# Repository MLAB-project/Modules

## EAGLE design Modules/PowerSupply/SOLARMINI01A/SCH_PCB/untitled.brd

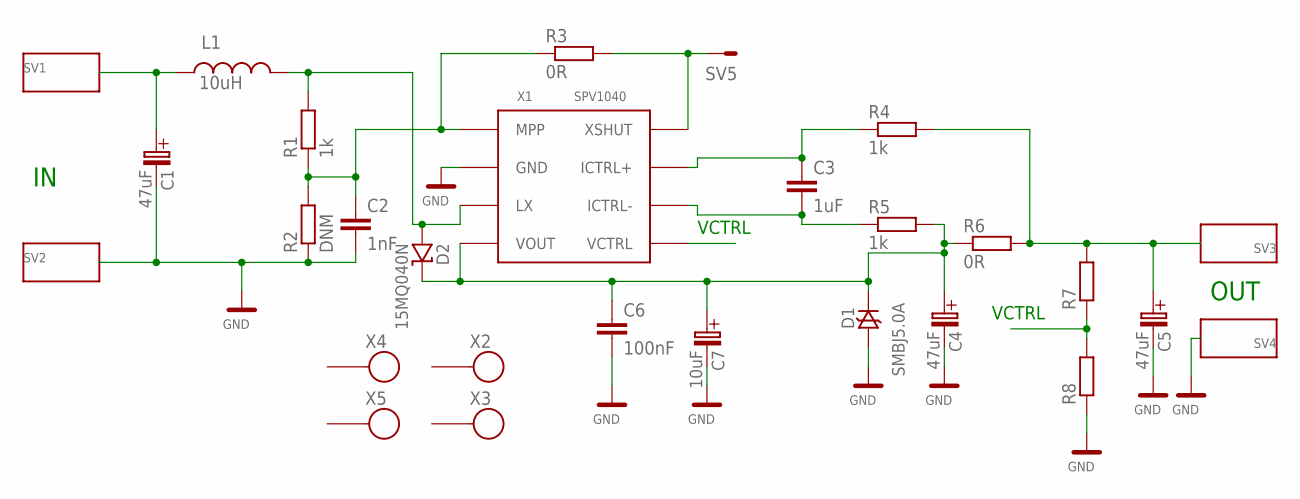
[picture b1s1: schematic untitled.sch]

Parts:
C1, C4, C5: 47uF; C
C2: 1nF; C0805
C3: 1uF; C0805
C6: 100nF; C0805
C7: 10uF; B
D1: SMBJ5.0A; SMB
D2: 15MQ040N; SMA
L1: 10uH; DE1205-10
R1, R4, R5: 1k; 0805
R2: DNM; 0805
R3, R6: 0R; 1206
R7, R8: R0805; 0805
SV1, SV2, SV3, SV4: WAGO256
SV5: MA01-1
X1: SPV1040; TSSOP8
X2, X3, X4, X5: SROUB3M

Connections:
GND: C1.- (C_EL-), C2.2, C4.- (C_EL-), C5.- (C_EL-), C6.2, C7.- (C_EL-), D1.A, R2.1, R8.1, SV2.1, SV2.A1, SV4.1, SV4.A1, X1.2 (GND)
unnamed: C1.+ (C_EL+), L1.P$1 (1), SV1.1, SV1.A1
unnamed: R3.2, SV5.1, X1.8 (XSHUT)
unnamed: C2.1, R1.1, R2.2, R3.1, X1.1 (MPP)
unnamed: C3.1, R4.1, X1.7 (ICTRL+)
unnamed: C4.+ (C_EL+), C6.1, C7.+ (C_EL+), D1.K, D2.K, R5.2, R6.1, X1.4 (VOUT)
unnamed: D2.A, L1.P$2 (2), R1.2, X1.3 (LX)
unnamed: C5.+ (C_EL+), R4.2, R6.2, R7.2, SV3.1, SV3.A1
unnamed: C3.2, R5.1, X1.6 (ICTRL-)
VCTRL: R7.1, R8.2, X1.5 (VCTRL)

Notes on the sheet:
VCTRL
OUT

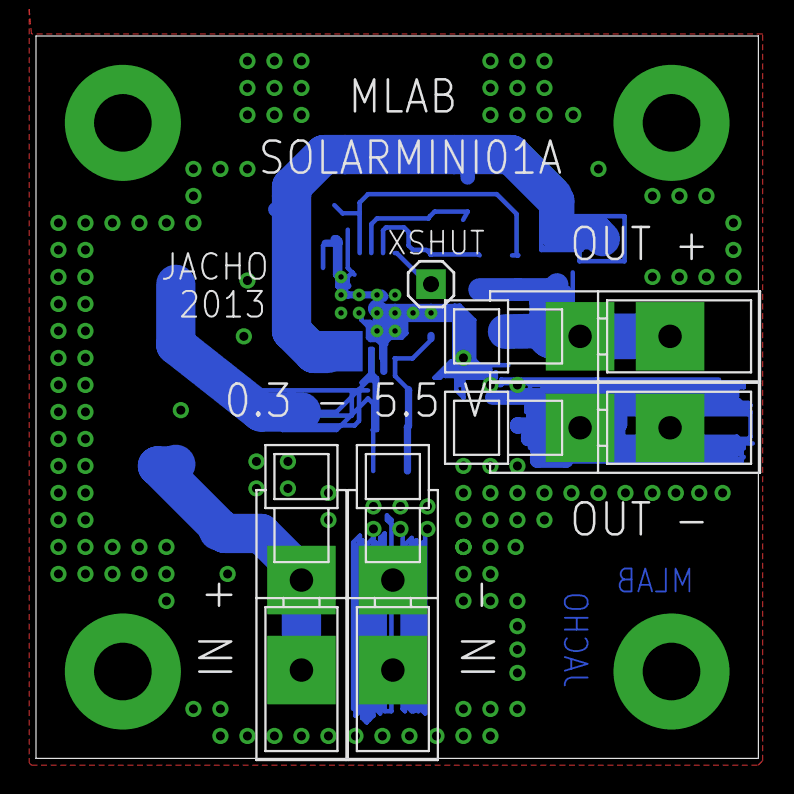
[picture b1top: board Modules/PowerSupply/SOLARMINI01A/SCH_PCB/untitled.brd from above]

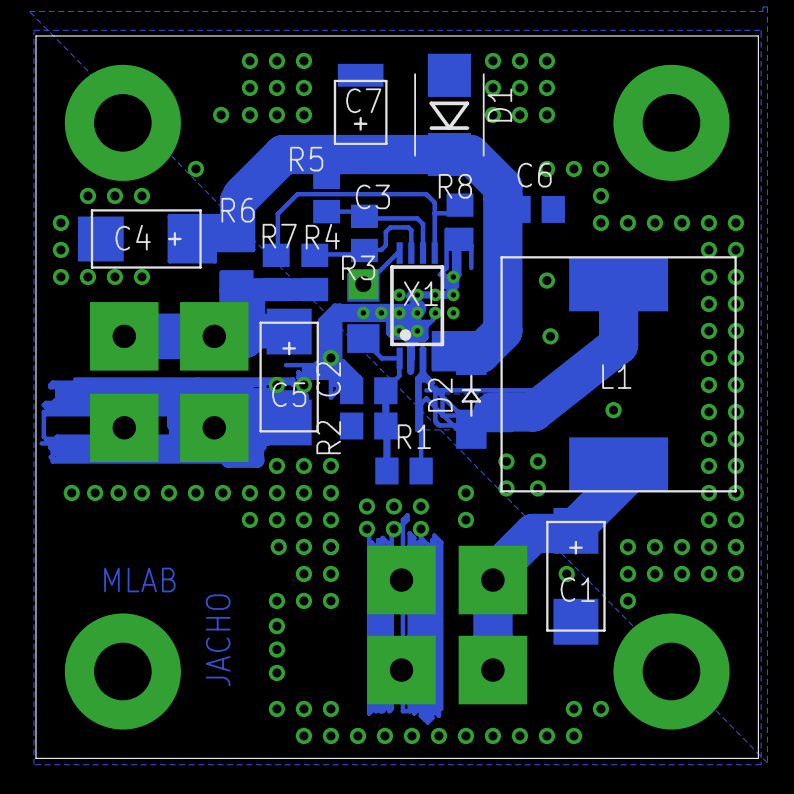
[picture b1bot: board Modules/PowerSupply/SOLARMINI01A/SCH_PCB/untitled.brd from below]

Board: 2 copper layers, 40.1 x 40.1 mm, 28 parts (19 on the bottom side), 10 nets.

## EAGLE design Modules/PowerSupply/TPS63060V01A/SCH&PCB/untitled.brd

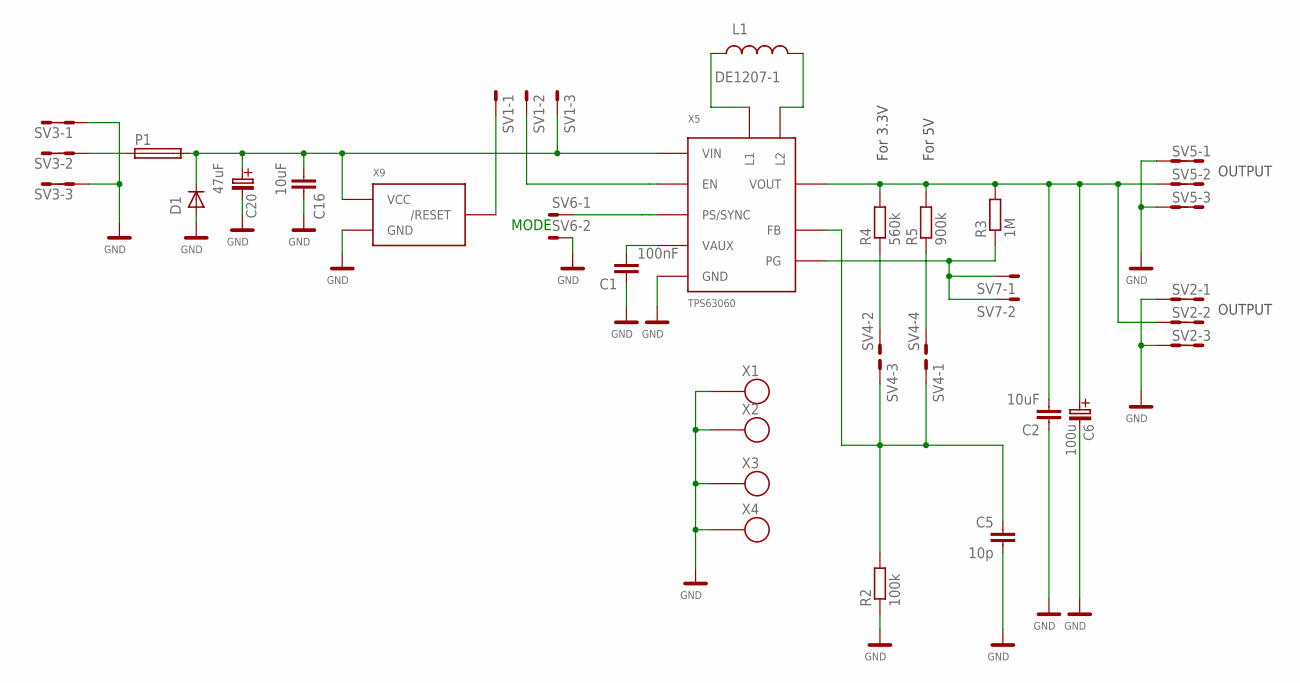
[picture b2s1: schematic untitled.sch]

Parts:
C1: 100nF; C0805
C2, C16: 10uF; C0805
C5: 10p; C0805
C6: 100u; C
C20: 47uF; B
D1: D-OB.SMA; SMA
L1: DE1207-1; DE1205-10
P1: POJISTKA_1812; 1812
R2: 100k; 0805
R3: 1M; 0805
R4: 560k; 0805
R5: 900k; 0805
SV1: MA03-1
SV2, SV3, SV5: MA03-2
SV4: MA02-3; MA02-2
SV6, SV7: MA02-1
X1, X2, X3, X4: SROUB3M
X5: TPS63060; SON10
X9: APX809-26SA; SOT23

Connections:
+BAT2: C16.2, C20.+ (C_EL+), D1.K (C), P1.2, SV1.3, X5.2 (VIN), X9.3 (VCC)
GND: C1.1, C2.1, C5.2, C6.- (C_EL-), C16.1, C20.- (C_EL-), D1.A, R2.1, SV2.1, SV2.2, SV2.5, SV2.6, SV3.1, SV3.2, SV3.5, SV3.6, SV5.1, SV5.2, SV5.5, SV5.6, SV6.2, X1.P$1, X2.P$1, X3.P$1, X4.P$1, X5.7 (GND), X5.11 (GND), X5.12 (GND), X5.13 (GND), X5.14 (GND), X5.15 (GND), X5.16 (GND), X5.17 (GND), X5.18 (GND), X5.19 (GND), X5.P$1 (GND), X5.P$2 (GND), X5.P$3 (GND), X5.P$4 (GND), X5.P$5 (GND), X9.1 (GND); also elsewhere on the board
unnamed: SV1.1, X9.2 (/RESET)
unnamed: SV1.2, X5.3 (EN)
unnamed: P1.1, SV3.3, SV3.4
unnamed: C5.1, R2.2, SV4.1, SV4.3, X5.8 (FB)
unnamed: R3.1, SV7.1, SV7.2, X5.5 (PG)
unnamed: R4.1, SV4.2
unnamed 8: C2.2, C6.+ (C_EL+), R3.2, R4.2, R5.2, SV2.3, SV2.4, SV5.3, SV5.4, X5.9 (VOUT); also elsewhere on the board
unnamed: R5.1, SV4.4
unnamed: SV6.1, X5.4 (PS/SYNC)
unnamed: C1.2, X5.6 (VAUX)
unnamed: L1.P$1 (1), X5.1 (L1)
unnamed: L1.P$2 (2), X5.10 (L2)

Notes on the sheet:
OUTPUT
MODE
For 5V
For 3.3V

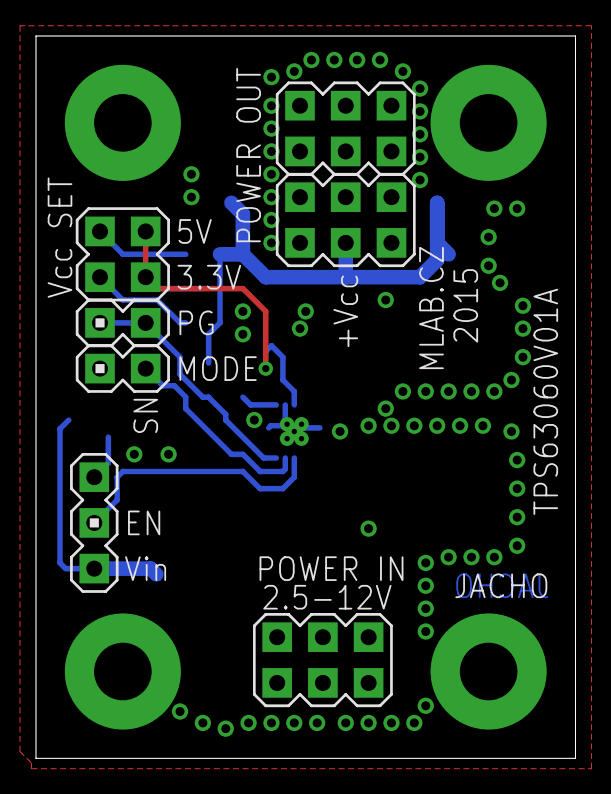
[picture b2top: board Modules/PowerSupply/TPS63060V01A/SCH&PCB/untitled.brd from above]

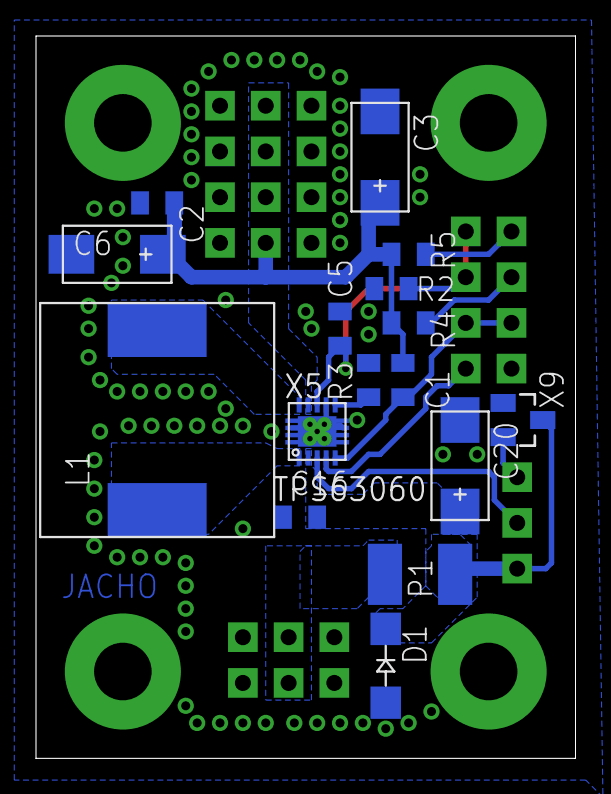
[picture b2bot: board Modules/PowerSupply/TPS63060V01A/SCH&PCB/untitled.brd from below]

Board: 2 copper layers, 30.0 x 40.1 mm, 27 parts (16 on the bottom side), 14 nets.

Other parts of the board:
C3: 47u; C

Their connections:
GND: C3.-; also elsewhere on the board
unnamed 8: C3.+; also elsewhere on the board

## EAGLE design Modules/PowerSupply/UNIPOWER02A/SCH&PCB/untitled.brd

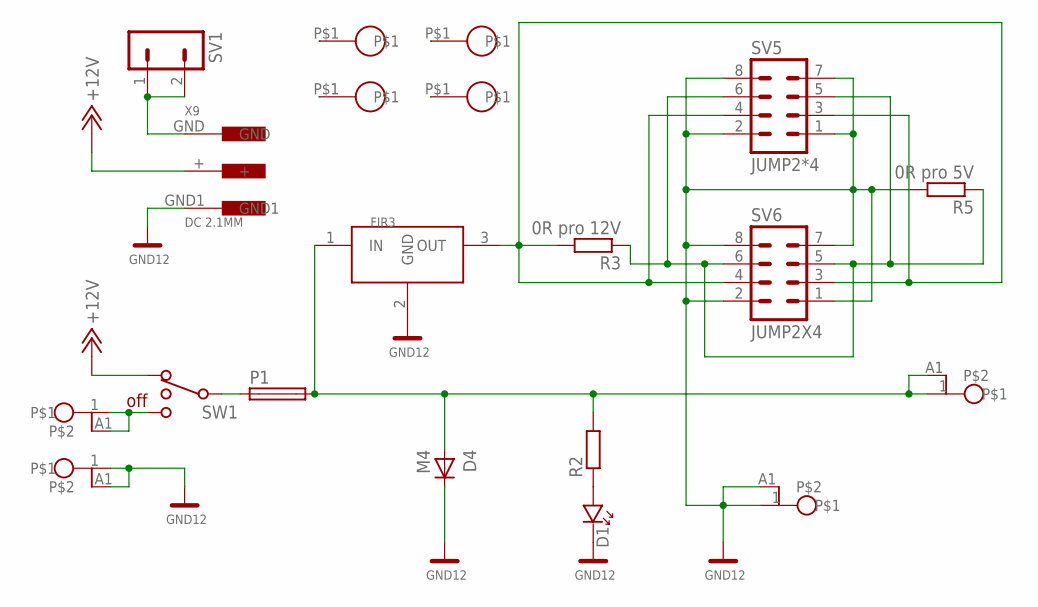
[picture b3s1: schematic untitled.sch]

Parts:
D1: D_LED_3MM; D_LED_3
D4: M4; SMA
FIR3: FILTR0805; F0805
P1: POJISTKA_1812; 1812
R2: R-EU_R0805; R0805
R3: 0R pro 12V; R0805
R5: 0R pro 5V; R0805
SV1: MA02-1
SV5: JUMP2*4; MA04-2
SV6: JUMP2X4; MA04-2
SW1: PREPINAC_POSUVNY_SL19-121; PREPINAC-POSUVNÝ
X1, X2, X3, X8: WAGO256
X4, X5, X6, X7: M3; SROUB3M
X9: DC 2.1MM; KONEKTOR_DC_2.1MM

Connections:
+12V: SW1.1 (3), X9.+
GND12: D1.K, D4.K (C), FIR3.2 (GND), R5.2, SV5.1, SV5.2, SV5.7, SV5.8, SV6.1, SV6.2, SV6.7, SV6.8, X2.1, X2.A1, X3.1, X3.A1, X9.GND1
unnamed: SW1.3 (1), X1.1, X1.A1
unnamed: D1.A, R2.1
unnamed: R3.1, R5.1, SV5.5, SV5.6, SV6.5, SV6.6
unnamed: SV1.1, SV1.2 (3), X9.GND
unnamed: FIR3.3 (OUT), R3.2, SV5.3, SV5.4, SV6.3, SV6.4
unnamed: P1.1, SW1.2
unnamed: D4.A, FIR3.1 (IN), P1.2, R2.2, X8.1, X8.A1

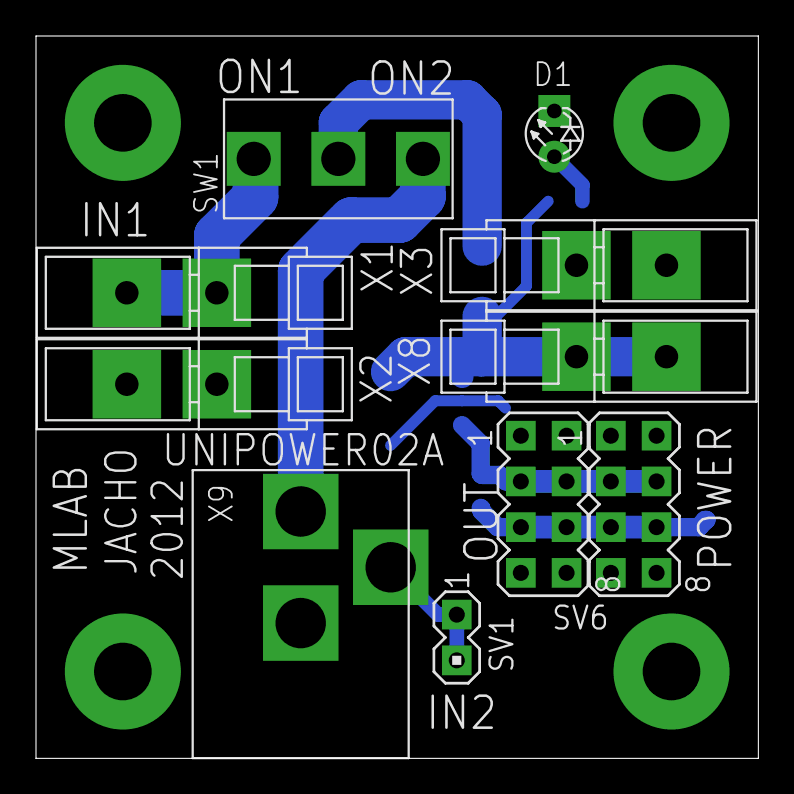
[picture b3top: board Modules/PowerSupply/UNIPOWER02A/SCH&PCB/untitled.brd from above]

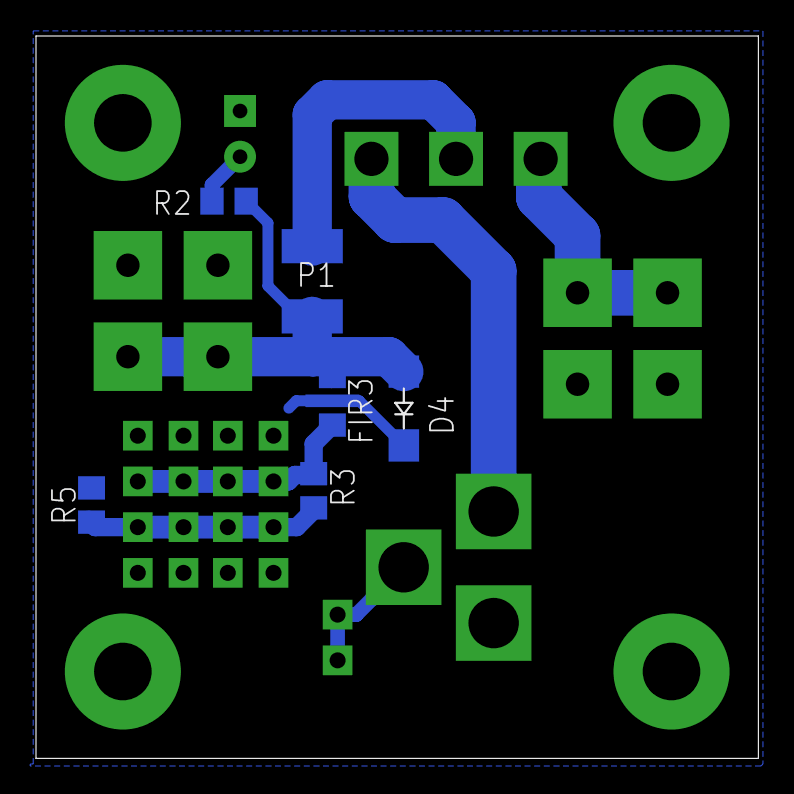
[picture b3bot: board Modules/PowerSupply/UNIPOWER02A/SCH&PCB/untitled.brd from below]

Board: 2 copper layers, 40.1 x 40.1 mm, 20 parts (6 on the bottom side), 9 nets.

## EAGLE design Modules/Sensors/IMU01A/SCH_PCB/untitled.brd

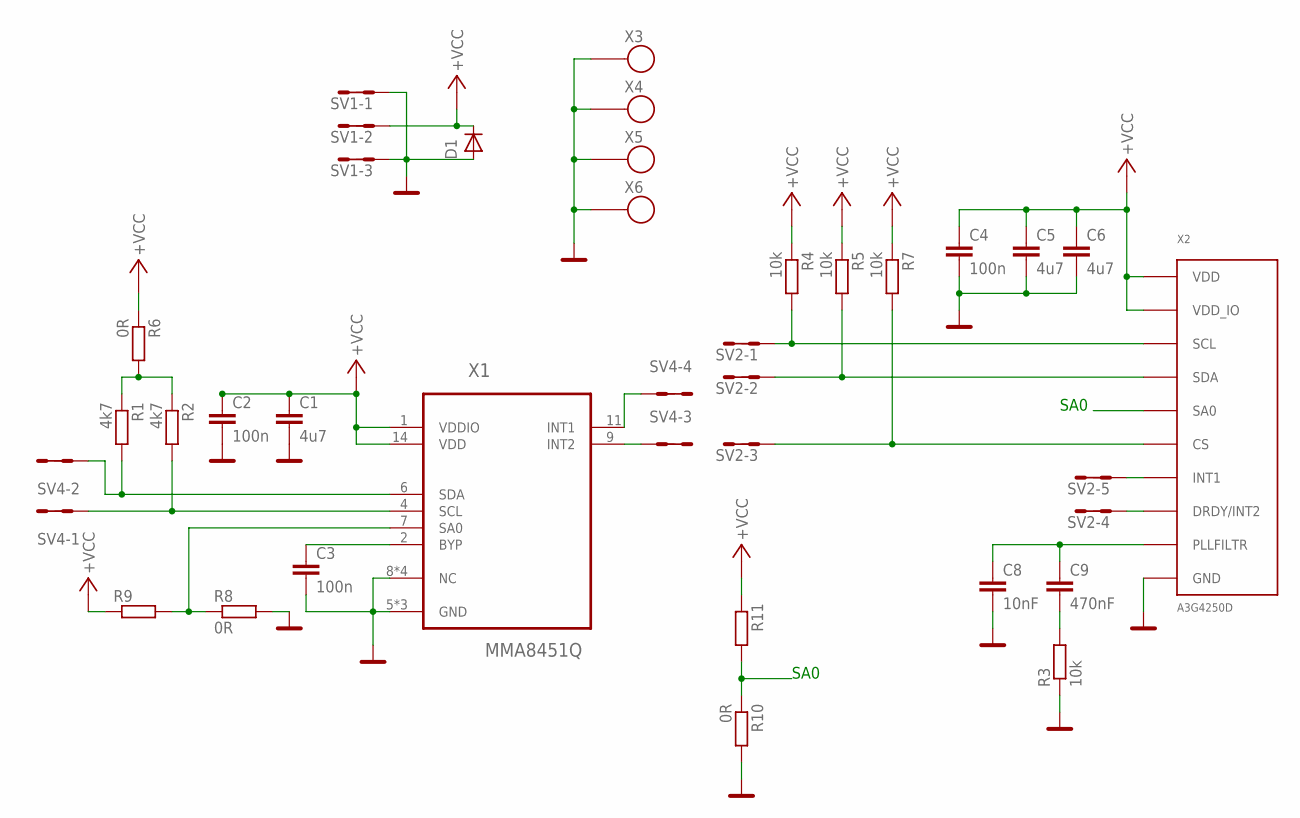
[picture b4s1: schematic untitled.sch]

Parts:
C1, C5, C6: 4u7; C0805
C2, C3, C4: 100n; C0805
C8: 10nF; C0805
C9: 470nF; C0805
D1: D-OB.SMA; SMA
R1, R2: 4k7; R0805
R3, R4, R5, R7: 10k; R0805
R6: 0R; R0805
R8, R10: 0R; 0805
R9, R11: R-EU_R2010; R2010
SV1: MA03-2
SV2: MA05-2
SV4: MA04-2
X1: MMA8451Q; QFN50P300X300X100-16N
X2: A3G4250D; LGA16
X3, X4, X5, X6: SROUB3M

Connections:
+VCC: C1.1, C2.1, C4.1, C5.1, C6.1, D1.K (C), R4.1, R5.1, R6.1, R7.1, R9.1, R11.1, SV1.3, SV1.4, X1.1 (VDDIO), X1.14 (VDD), X2.1 (VDD_IO), X2.15 (VDD), X2.16 (VDD)
GND: C1.2, C2.2, C3.2, C4.2, C5.2, C6.2, C8.2, D1.A, R3.1, R8.2, R10.2, SV1.1, SV1.2, SV1.5, SV1.6, X1.5 (GND), X1.8 (NC), X1.10 (GND), X1.12 (GND), X1.13 (NC), X1.15 (NC), X1.16 (NC), X2.8 (GND), X2.9 (GND), X2.10 (GND), X2.11 (GND), X2.12 (GND), X2.13 (GND), X3.P$1, X4.P$1, X5.P$1, X6.P$1
unnamed: R1.2, SV4.3, SV4.4, X1.6 (SDA)
unnamed: R2.2, SV4.1, SV4.2, X1.4 (SCL)
unnamed: R8.1, R9.2, X1.7 (SA0)
unnamed: C8.1, C9.1, X2.14 (PLLFILTR)
unnamed: C3.1, X1.2 (BYP)
unnamed: R1.1, R2.1, R6.2
unnamed: SV4.5, SV4.6, X1.9 (INT2)
unnamed: R7.2, SV2.5, SV2.6, X2.5 (CS)
unnamed: SV2.9, SV2.10, X2.7 (INT1)
unnamed: SV2.7, SV2.8, X2.6 (DRDY/INT2)
unnamed: SV4.7, SV4.8, X1.11 (INT1)
unnamed: R4.2, SV2.1, SV2.2, X2.2 (SCL)
unnamed: C9.2, R3.2
unnamed: R5.2, SV2.3, SV2.4, X2.3 (SDA)
SA0: R10.1, R11.2, X2.4 (SA0)

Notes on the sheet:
SA0

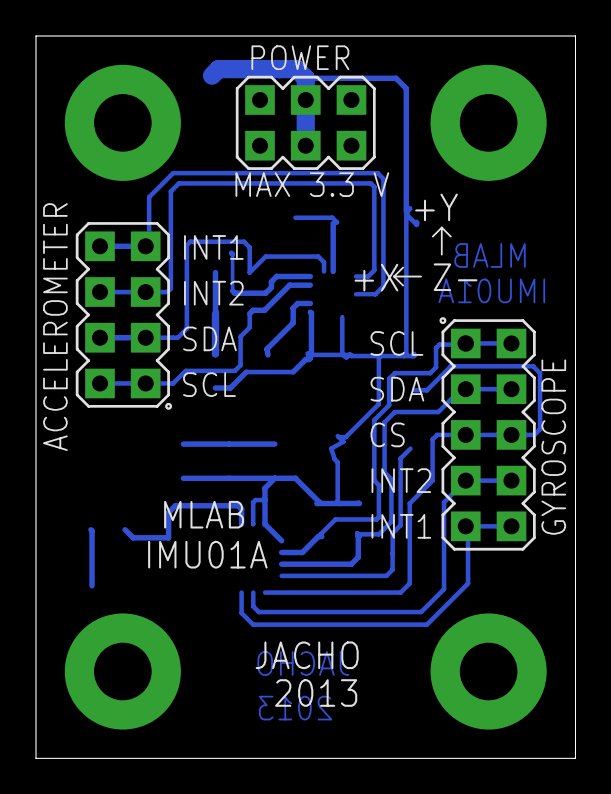
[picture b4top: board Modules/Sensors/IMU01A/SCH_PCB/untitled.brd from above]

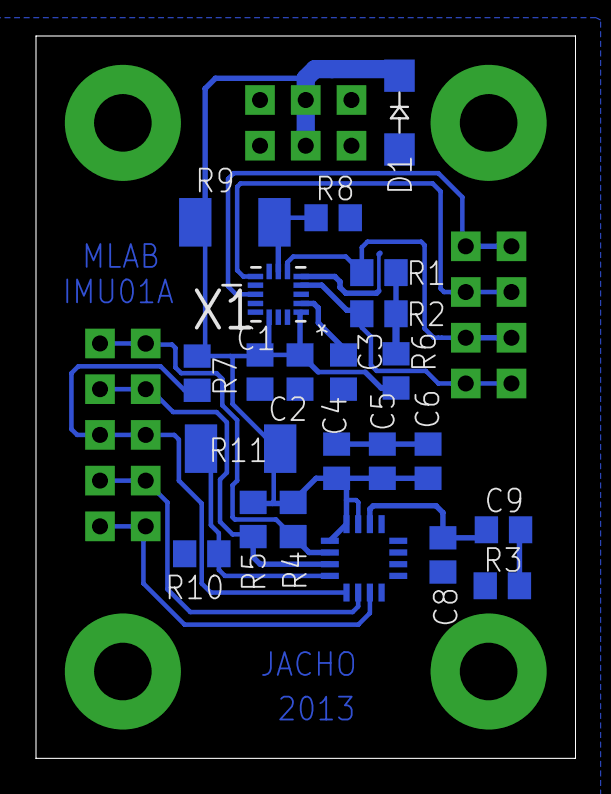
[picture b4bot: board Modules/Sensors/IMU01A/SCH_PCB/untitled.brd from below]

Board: 2 copper layers, 30.0 x 40.1 mm, 29 parts (22 on the bottom side), 17 nets.

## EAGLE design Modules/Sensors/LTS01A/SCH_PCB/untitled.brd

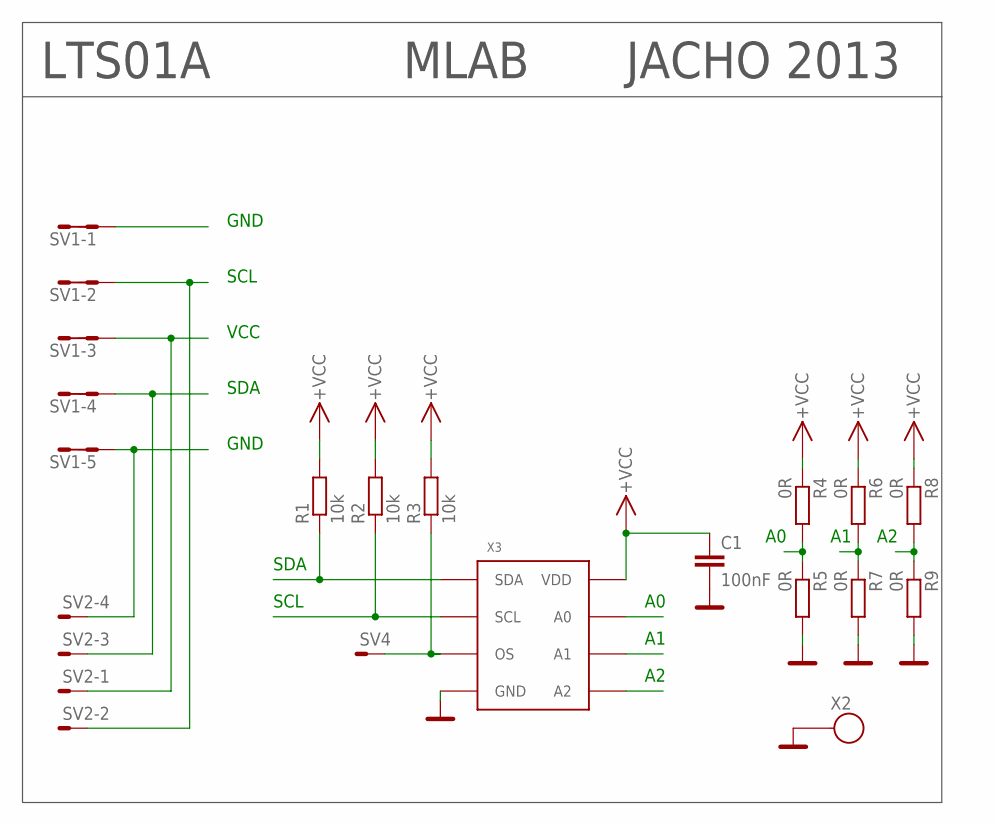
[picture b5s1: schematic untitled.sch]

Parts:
C1: 100nF; C0603
R1, R2, R3: 10k; R0603
R4, R5, R6, R7, R8, R9: 0R; R0603
SV1: MA06-2
SV2: SMD_MA04-01; SMD_MA04-1
SV4: MA01-1
X2: SROUB3M
X3: MAX31725; TDFN8

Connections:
A0: R4.2, R5.1, X3.7 (A0)
A1: R6.2, R7.1, X3.6 (A1)
A2: R8.2, R9.1, X3.5 (A2)
GND: C1.2, R5.2, R7.2, R9.2, SV1.1, SV1.2, SV1.9, SV1.10, SV2.4, X2.P$1, X3.4 (GND), X3.9 (GND)
OS: R3.1, SV4.1, X3.3 (OS)
SCL: R2.1, SV1.3, SV1.4, SV2.2, X3.2 (SCL)
SDA: R1.1, SV1.7, SV1.8, SV2.3, X3.1 (SDA)
VCC: C1.1, R1.2, R2.2, R3.2, R4.1, R6.1, R8.1, SV1.5, SV1.6, SV2.1, X3.8 (VDD)

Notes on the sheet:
VCC
GND
SCL
SDA
LTS01A
MLAB
JACHO 2013

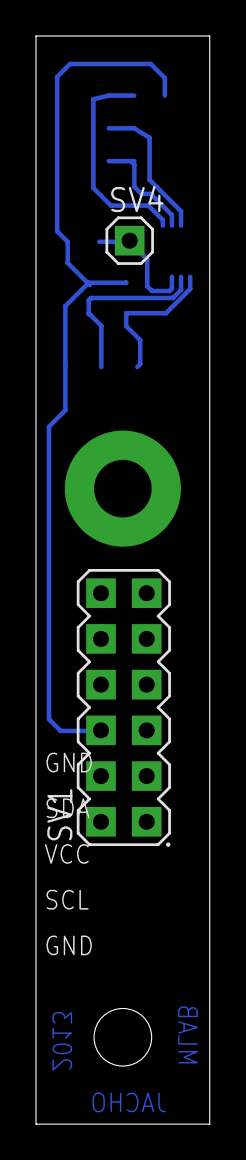
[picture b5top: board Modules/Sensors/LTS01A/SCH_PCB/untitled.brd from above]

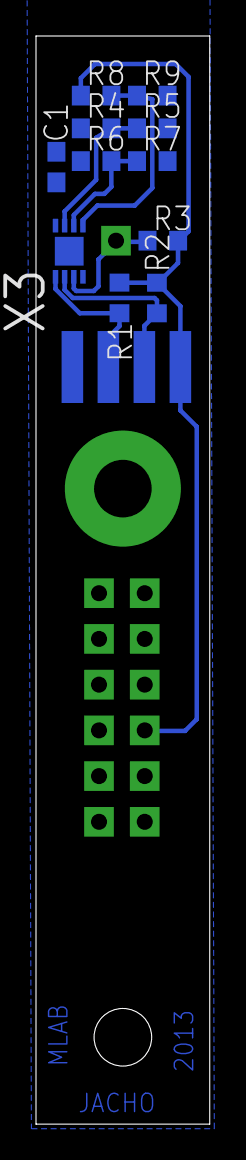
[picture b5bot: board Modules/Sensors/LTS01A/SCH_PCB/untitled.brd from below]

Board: 2 copper layers, 9.7 x 60.5 mm, 15 parts (12 on the bottom side), 8 nets.

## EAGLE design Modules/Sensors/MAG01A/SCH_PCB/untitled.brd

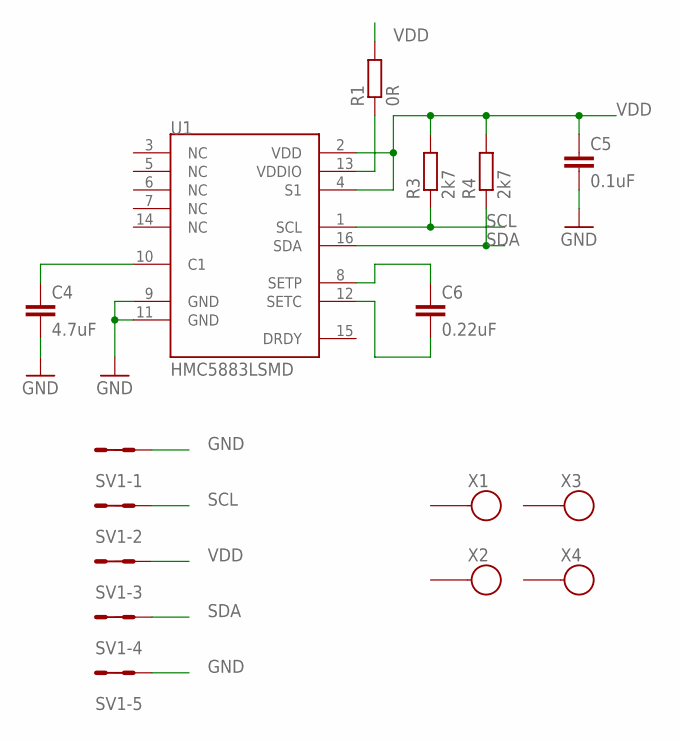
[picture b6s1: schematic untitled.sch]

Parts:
C4: 4.7uF; C0805
C5: 0.1uF; C0805
C6: 0.22uF; C0805
R1: 0R; 1206
R3, R4: 2k7; 0805
SV1: MA05-2
U1: HMC5883LSMD; 16LPCC
X1, X2, X3, X4: SROUB3M

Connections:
GND: C4.2, C5.2, SV1.1, SV1.2, SV1.9, SV1.10, U1.9 (GND), U1.11 (GND)
unnamed: C4.1, U1.10 (C1)
unnamed: R1.1, U1.13 (VDDIO)
unnamed: C6.1, U1.8 (SETP)
unnamed: C6.2, U1.12 (SETC)
SCL: R3.1, SV1.3, SV1.4, U1.1 (SCL)
SDA: R4.1, SV1.7, SV1.8, U1.16 (SDA)
VDD: C5.1, R1.2, R3.2, R4.2, SV1.5, SV1.6, U1.2 (VDD), U1.4 (S1)

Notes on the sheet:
GND
SCL
VDD
SDA

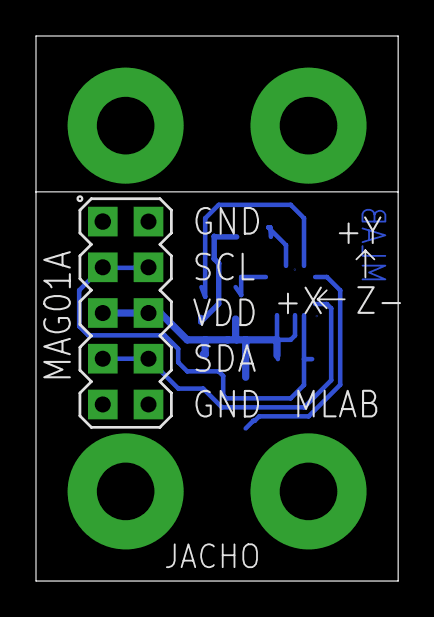
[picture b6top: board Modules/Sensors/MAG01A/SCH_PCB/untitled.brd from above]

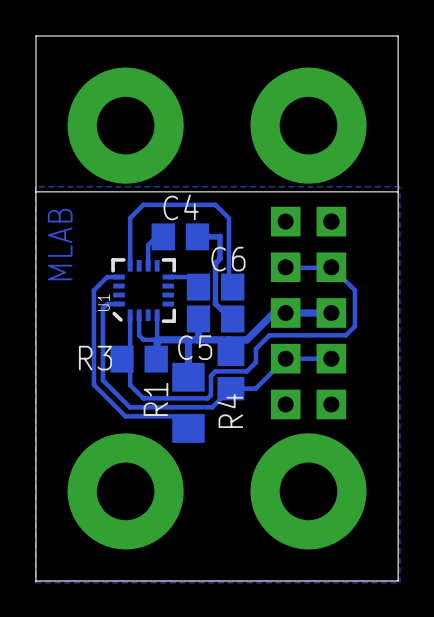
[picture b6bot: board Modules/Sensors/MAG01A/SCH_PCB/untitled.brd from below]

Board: 2 copper layers, 20.1 x 30.3 mm, 12 parts (7 on the bottom side), 8 nets.

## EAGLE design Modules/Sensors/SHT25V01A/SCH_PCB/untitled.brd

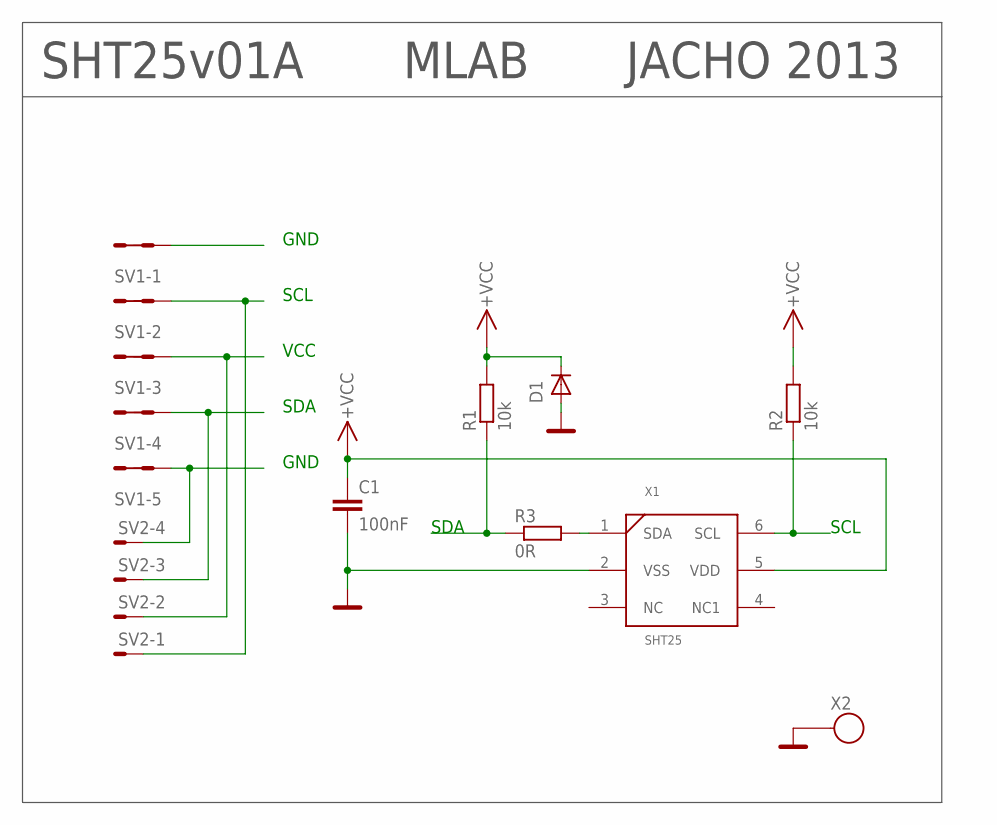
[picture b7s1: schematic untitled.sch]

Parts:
C1: 100nF; C0805
D1: D-OB.SMA; SMA
R1, R2: 10k; R0805
R3: 0R; R0805
SV1: MA05-2
SV2: SMD_MA04-01; SMD_MA04-1
X1: SHT25
X2: SROUB3M

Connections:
GND: C1.2, D1.A, SV1.1, SV1.2, SV1.9, SV1.10, SV2.4, X1.2 (VSS), X2.P$1
unnamed: R3.2, X1.1 (SDA)
SCL: R2.1, SV1.3, SV1.4, SV2.1, X1.6 (SCL)
SDA: R1.1, R3.1, SV1.7, SV1.8, SV2.3
VCC: C1.1, D1.K (C), R1.2, R2.2, SV1.5, SV1.6, SV2.2, X1.5 (VDD)

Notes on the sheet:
VCC
GND
SCL
SDA
SHT25v01A
MLAB
JACHO 2013

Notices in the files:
parts and their libraries:
PaJa_22: Copyright (C) PaJa 2001-2010
